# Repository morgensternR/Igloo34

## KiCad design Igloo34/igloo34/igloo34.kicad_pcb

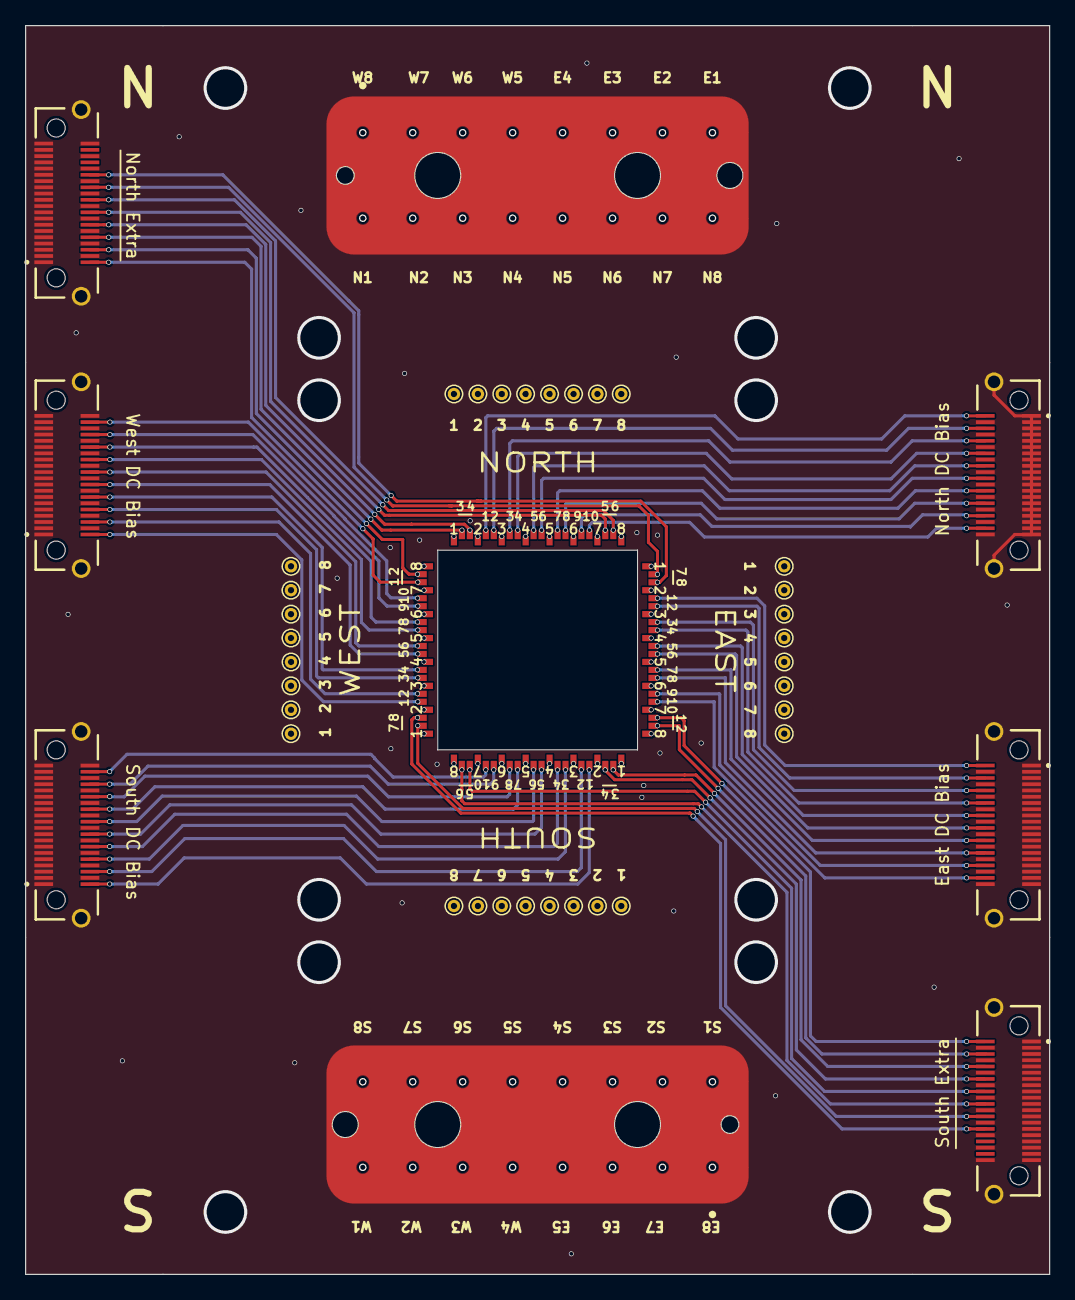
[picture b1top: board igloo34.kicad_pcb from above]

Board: 4 copper layers, 82.0 x 100.0 mm, 56 parts (0 on the bottom side), 89 nets.

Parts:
J1, J2, J5, J6: Conn_01x08_Pin; wirebond_8x_25mm
J3, J4: BE40A-S-92SP-2-2-08-0152; BE40A-S-92SP-X-2-08
J7, J8, J11, J12, J15, J20: LSHM-120-02.5-L-DV-A-S-TR; SAMTEC_LSHM-120-02.5-L-DV-A-S-TR
J9, J10, J13, J14: Conn_01x10; wirebond_10x_1cm
J16, J17, J18, J19, J21, J22, J23, J24: Conn_01x02; wirebond_2x_500um
TP1, TP2, TP3, TP4, TP5, TP6, TP7, TP8, TP9, TP10, TP11, TP12, TP13, TP14, TP15, TP16, TP17, TP18, TP19, TP20, TP21, TP22, TP23, TP24, TP25, TP26, TP27, TP28, TP29, TP30, TP31, TP32: TestPoint; Test point top pad

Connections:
GND: J3.S1 (SHIELD), J4.S1 (SHIELD), J7.01, J7.03, J7.04, J7.05, J7.07, J7.08, J7.09, J7.11, J7.12, J7.13, J7.15, J7.16, J7.17, J7.19, J7.20, J7.21, J7.23, J7.24, J7.25, J7.27, J7.28, J7.29, J7.31, J7.32, J7.33, J7.35, J7.36, J7.37, J7.39, J7.40, J7.S1 (SHIELD), J7.S2 (SHIELD), J8.01, J8.03, J8.04, J8.05, J8.07, J8.08, J8.09, J8.11, J8.12, J8.13, J8.15, J8.16, J8.17, J8.19, J8.20, J8.21, J8.23, J8.24, J8.25, J8.27, J8.28, J8.29, J8.31, J8.32, J8.33, J8.35, J8.36, J8.37, J8.39, J8.40, J8.S1 (SHIELD), J8.S2 (SHIELD), J11.01, J11.03, J11.04, J11.05, J11.07, J11.08, J11.09, J11.11, J11.12, J11.13, J11.15, J11.16, J11.17, J11.19, J11.20, J11.21, J11.23, J11.24, J11.25, J11.27, J11.28, J11.29, J11.31, J11.32, J11.33, J11.35, J11.36, J11.37, J11.39, J11.40, J11.S1 (SHIELD), J11.S2 (SHIELD), J12.01, J12.03, J12.04, J12.05, J12.07, J12.08, J12.09, J12.11, J12.12, J12.13, J12.15, J12.16, J12.17, J12.19, J12.20, J12.21, J12.23, J12.24, J12.25, J12.27, J12.28, J12.29, J12.31, J12.32, J12.33, J12.35, J12.36, J12.37, J12.39, J12.40, J12.S1 (SHIELD), J12.S2 (SHIELD), J15.01, J15.03, J15.04, J15.05, J15.07, J15.08, J15.09, J15.11, J15.12, J15.13, J15.15, J15.16, J15.17, J15.19, J15.20, J15.21, J15.23, J15.24, J15.25, J15.27, J15.28, J15.29, J15.31, J15.32, J15.33, J15.35, J15.36, J15.37, J15.39, J15.40, J15.S1 (SHIELD), J15.S2 (SHIELD), J20.01, J20.03, J20.04, J20.05, J20.07, J20.08, J20.09, J20.11, J20.12, J20.13, J20.15, J20.16, J20.17, J20.19, J20.20, J20.21, J20.23, J20.24, J20.25, J20.27, J20.28, J20.29, J20.31, J20.32, J20.33, J20.35, J20.36, J20.37, J20.39, J20.40, J20.S1 (SHIELD), J20.S2 (SHIELD)
unnamed: J1.1, J3.A01, TP32.1
unnamed: J1.2, J3.A02, TP31.1
unnamed: J1.3, J3.A03, TP30.1
unnamed: J1.4, J3.A04, TP29.1
unnamed: J1.5, J4.A05, TP20.1
unnamed: J1.6, J4.A06, TP19.1
unnamed: J1.7, J4.A07, TP18.1
unnamed: J1.8, J4.A08, TP17.1
unnamed: J2.1, J4.A01, TP24.1
unnamed: J2.2, J4.A02, TP23.1
unnamed: J2.3, J4.A03, TP22.1
unnamed: J2.4, J4.A04, TP21.1
unnamed: J2.5, J3.A05, TP28.1
unnamed: J2.6, J3.A06, TP27.1
unnamed: J2.7, J3.A07, TP26.1
unnamed: J2.8, J3.A08, TP25.1
unnamed: J3.B01, J5.1, TP9.1
unnamed: J3.B02, J5.2, TP10.1
unnamed: J3.B03, J5.3, TP11.1
unnamed: J3.B04, J5.4, TP12.1
unnamed: J3.B05, J5.5, TP13.1
unnamed: J3.B06, J5.6, TP14.1
unnamed: J3.B07, J5.7, TP15.1
unnamed: J3.B08, J5.8, TP16.1
unnamed: J4.B01, J6.1, TP2.1
unnamed: J4.B02, J6.2, TP1.1
unnamed: J4.B03, J6.3, TP3.1
unnamed: J4.B04, J6.4, TP4.1
unnamed: J4.B05, J6.5, TP5.1
unnamed: J4.B06, J6.6, TP6.1
unnamed: J4.B07, J6.7, TP7.1
unnamed: J4.B08, J6.8, TP8.1
unnamed: J7.02, J9.1
unnamed: J7.06, J9.2
unnamed: J7.10, J9.3
unnamed: J7.14, J9.4
unnamed: J7.18, J9.5
unnamed: J7.22, J9.6
unnamed: J7.26, J9.7
unnamed: J7.30, J9.8
unnamed: J7.34, J9.9
unnamed: J7.38, J9.10
unnamed: J8.02, J10.1
unnamed: J8.06, J10.2
unnamed: J8.10, J10.3
unnamed: J8.14, J10.4
unnamed: J8.18, J10.5
unnamed: J8.22, J10.6
unnamed: J8.26, J10.7
unnamed: J8.30, J10.8
unnamed: J8.34, J10.9
unnamed: J8.38, J10.10
unnamed: J11.02, J13.1
unnamed: J11.06, J13.2
unnamed: J11.10, J13.3
unnamed: J11.14, J13.4
unnamed: J11.18, J13.5
unnamed: J11.22, J13.6
unnamed: J11.26, J13.7
unnamed: J11.30, J13.8
unnamed: J11.34, J13.9
unnamed: J11.38, J13.10
unnamed: J12.02, J14.1
unnamed: J12.06, J14.2
unnamed: J12.10, J14.3
unnamed: J12.14, J14.4
unnamed: J12.18, J14.5
unnamed: J12.22, J14.6
unnamed: J12.26, J14.7
unnamed: J12.30, J14.8
unnamed: J12.34, J14.9
unnamed: J12.38, J14.10
unnamed: J15.02, J16.1
unnamed: J15.06, J16.2
unnamed: J15.10, J17.1
unnamed: J15.14, J17.2
unnamed: J15.18, J18.1
unnamed: J15.22, J18.2
unnamed: J15.26, J19.1
unnamed: J15.30, J19.2
unnamed: J20.02, J21.1
unnamed: J20.06, J21.2
unnamed: J20.10, J22.1
unnamed: J20.14, J22.2
unnamed: J20.18, J23.1
unnamed: J20.22, J23.2
unnamed: J20.26, J24.1
unnamed: J20.30, J24.2

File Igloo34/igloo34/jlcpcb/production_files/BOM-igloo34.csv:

Comment,Designator,Footprint,LCSC
LSHM-120-02.5-L-DV-A-S-TR,"J11,J12,J15,J20,J7,J8",SAMTEC_LSHM-120-02.5-L-DV-A-S-TR,C3654193
BE40A-S-92SP-2-2-08-0152,J3,BE40A-S-92SP-X-2-08,
TestPoint,TP32,Test point top pad,
TestPoint,TP31,Test point top pad,
TestPoint,TP30,Test point top pad,
TestPoint,TP29,Test point top pad,
TestPoint,TP28,Test point top pad,
TestPoint,TP27,Test point top pad,
TestPoint,TP26,Test point top pad,
TestPoint,TP25,Test point top pad,
TestPoint,TP24,Test point top pad,
TestPoint,TP23,Test point top pad,
TestPoint,TP22,Test point top pad,
TestPoint,TP21,Test point top pad,
TestPoint,TP20,Test point top pad,
TestPoint,TP19,Test point top pad,
TestPoint,TP18,Test point top pad,
TestPoint,TP17,Test point top pad,
TestPoint,TP16,Test point top pad,
TestPoint,TP15,Test point top pad,
TestPoint,TP14,Test point top pad,
TestPoint,TP13,Test point top pad,
TestPoint,TP12,Test point top pad,
TestPoint,TP11,Test point top pad,
TestPoint,TP10,Test point top pad,
TestPoint,TP9,Test point top pad,
TestPoint,TP8,Test point top pad,
TestPoint,TP7,Test point top pad,
TestPoint,TP6,Test point top pad,
TestPoint,TP5,Test point top pad,
TestPoint,TP4,Test point top pad,
TestPoint,TP3,Test point top pad,
TestPoint,TP2,Test point top pad,
TestPoint,TP1,Test point top pad,
Conn_01x02,J21,wirebond_2x_500um,
Conn_01x02,J17,wirebond_2x_500um,
Conn_01x08_Pin,J6,wirebond_8x_25mm,
Conn_01x02,J24,wirebond_2x_500um,
Conn_01x02,J18,wirebond_2x_500um,
Conn_01x02,J19,wirebond_2x_500um,
Conn_01x08_Pin,J2,wirebond_8x_25mm,
Conn_01x02,J23,wirebond_2x_500um,
Conn_01x02,J22,wirebond_2x_500um,
Conn_01x08_Pin,J5,wirebond_8x_25mm,
Conn_01x02,J16,wirebond_2x_500um,
Conn_01x10,J10,wirebond_10x_1cm,
Conn_01x10,J14,wirebond_10x_1cm,
Conn_01x10,J9,wirebond_10x_1cm,
BE40A-S-92SP-2-2-08-0152,J4,BE40A-S-92SP-X-2-08,
Conn_01x08_Pin,J1,wirebond_8x_25mm,
Conn_01x10,J13,wirebond_10x_1cm,

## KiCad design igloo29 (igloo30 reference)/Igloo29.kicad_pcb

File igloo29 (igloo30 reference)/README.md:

# Project/path setup
- Open amcc-template.kicad_pro, save as new project name

# Adding footprint+symbols
- Any footprint files added to /project-footprints/ will be added automatically to the "project-footprints" library
- Add any kicad_sym files to /project-symbols/ and add their path directly to Symbol Libraries:  Menu->Preferences->Manage Symbol Libraries
    - Suggested name:  "project-symbols2", "project-symbols3", etc
    - Whenever searching for symbols/footprints, just type "project" in the search bar

# To insert your new symbol + footprint
- Click Add Symbol button on right
- Navigate to e.g. "project-symbols2" and select the symbol
- Place the device, and double-click it to open properties
- Edit the "Footprint" field and navigate to e.g. "project-footprints" to select the footprint

# Before starting
- PCBNew->Menu->File->Board Setup
    - Physical Stackup -> 2 or 4 layers
    - Net Classes:
        - JLCPCB Stripline 50 Ohm trace width = 0.35mm wide
        - Via size/hole = 0.6mm/0.4mm

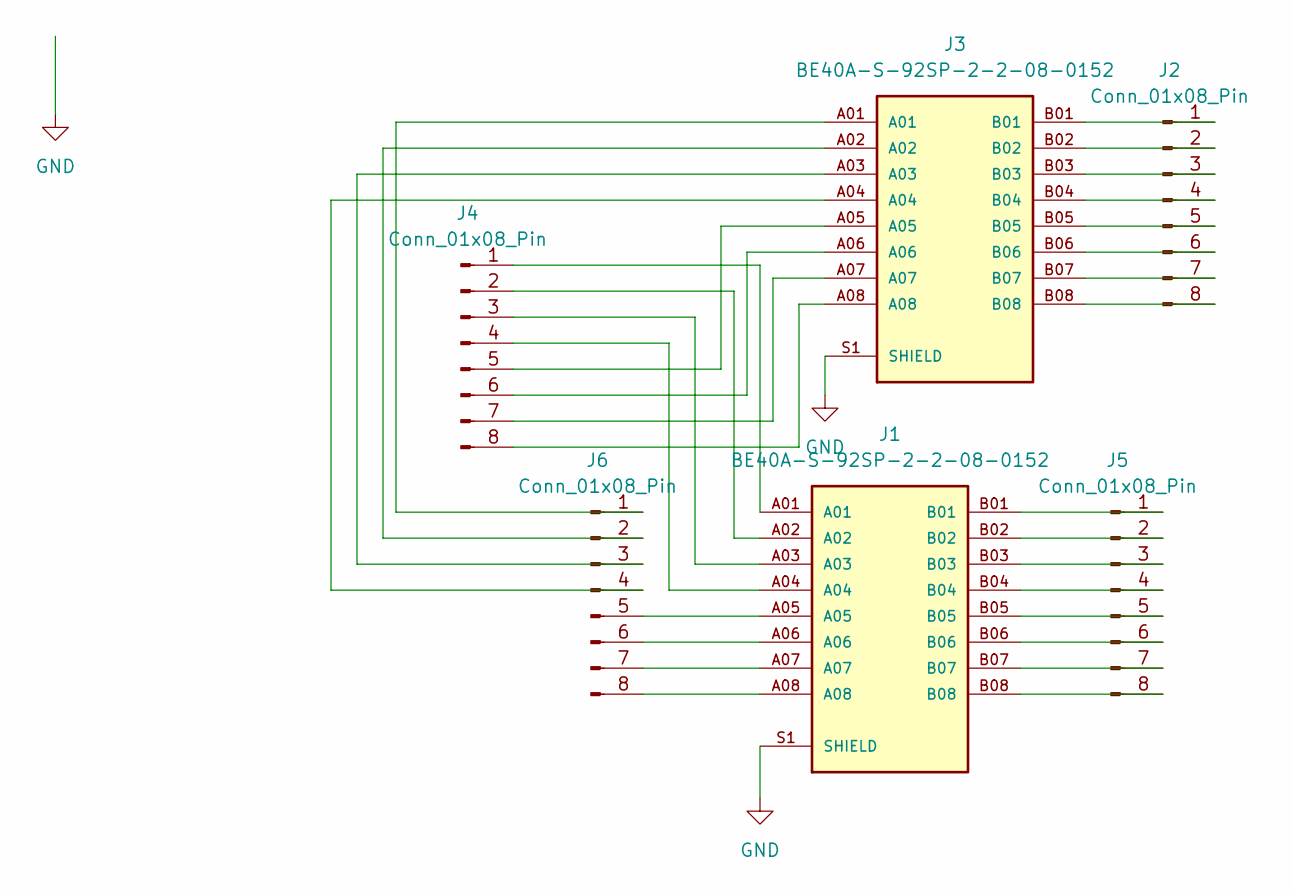
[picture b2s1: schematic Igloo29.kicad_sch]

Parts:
J1, J3: BE40A-S-92SP-2-2-08-0152; BE40A-S-92SP-X-2-08
J2, J4, J5, J6: Conn_01x08_Pin; wirebond_8x_25mm

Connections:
GND: J1.S1 (SHIELD), J3.S1 (SHIELD)
unnamed: J2.1, J3.B01
unnamed: J2.2, J3.B02
unnamed: J2.3, J3.B03
unnamed: J2.4, J3.B04
unnamed: J2.5, J3.B05
unnamed: J2.6, J3.B06
unnamed: J2.7, J3.B07
unnamed: J2.8, J3.B08
unnamed: J1.A01, J4.1
unnamed: J1.A02, J4.2
unnamed: J1.A03, J4.3
unnamed: J1.A04, J4.4
unnamed: J3.A05, J4.5
unnamed: J3.A06, J4.6
unnamed: J3.A07, J4.7
unnamed: J3.A08, J4.8
unnamed: J1.B01, J5.1
unnamed: J1.B02, J5.2
unnamed: J1.B03, J5.3
unnamed: J1.B04, J5.4
unnamed: J1.B05, J5.5
unnamed: J1.B06, J5.6
unnamed: J1.B07, J5.7
unnamed: J1.B08, J5.8
unnamed: J3.A01, J6.1
unnamed: J3.A02, J6.2
unnamed: J3.A03, J6.3
unnamed: J3.A04, J6.4
unnamed: J1.A05, J6.5
unnamed: J1.A06, J6.6
unnamed: J1.A07, J6.7
unnamed: J1.A08, J6.8

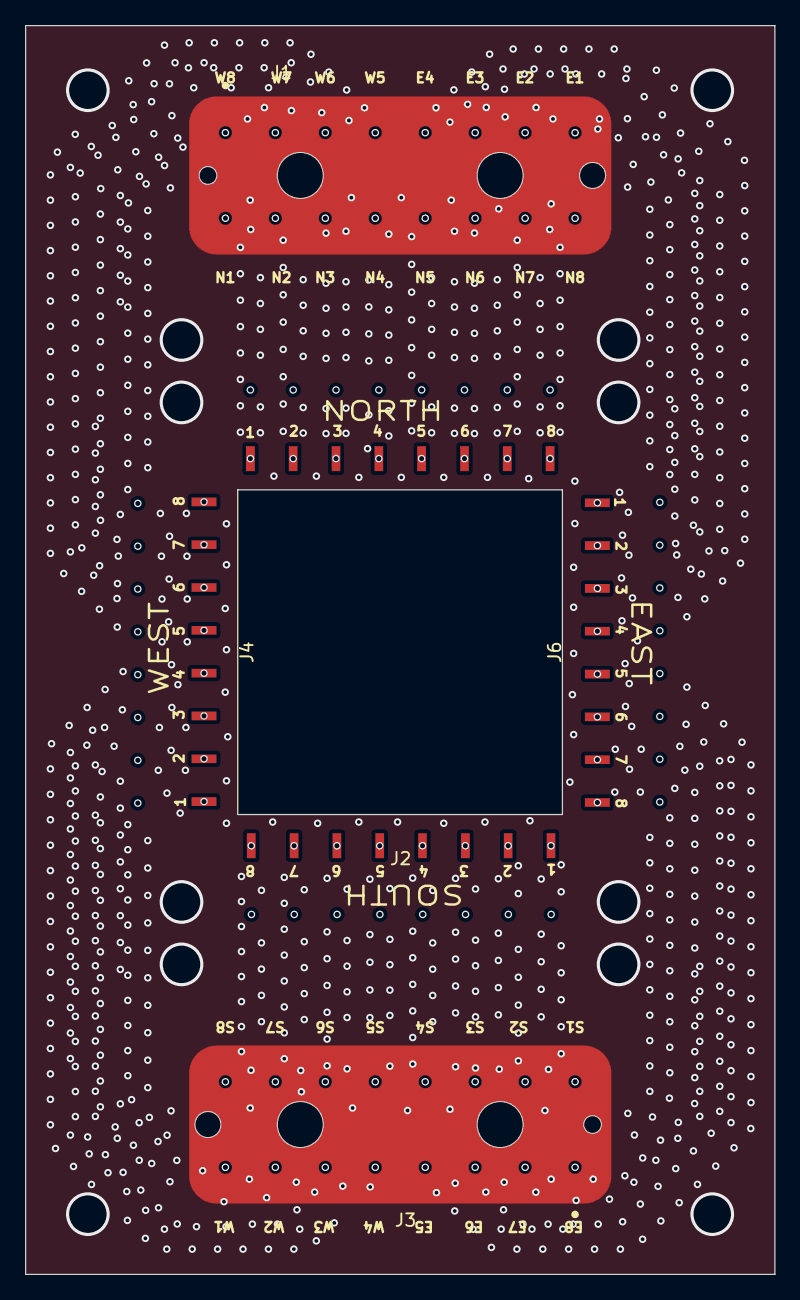
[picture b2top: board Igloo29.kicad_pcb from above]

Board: 4 copper layers, 60.0 x 100.0 mm, 6 parts (0 on the bottom side), 33 nets.

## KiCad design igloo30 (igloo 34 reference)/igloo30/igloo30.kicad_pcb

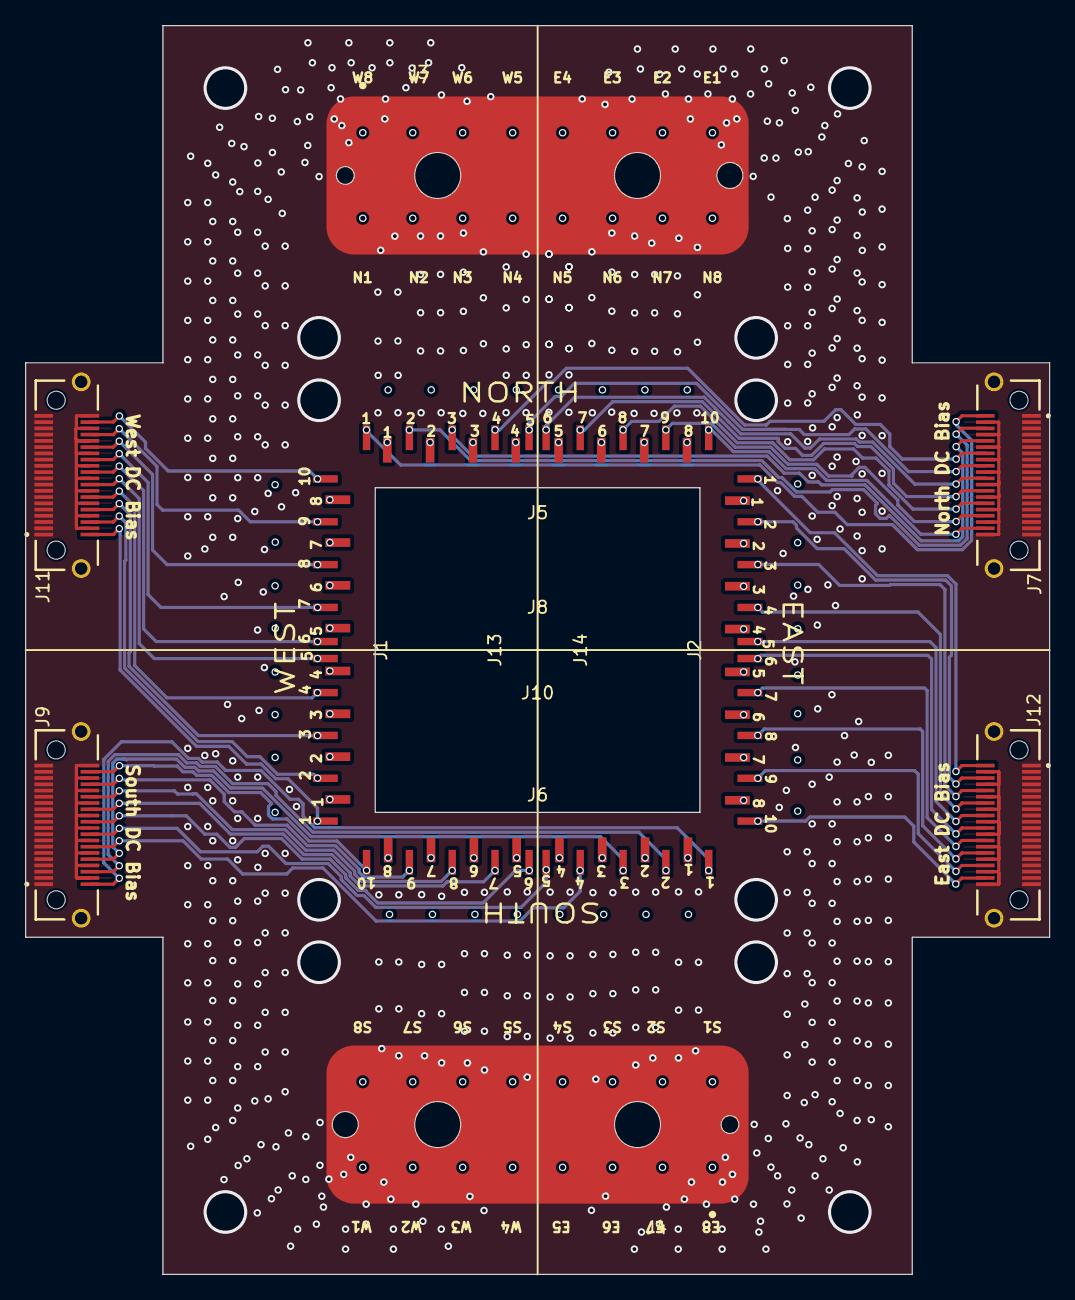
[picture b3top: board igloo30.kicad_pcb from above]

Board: 4 copper layers, 82.0 x 100.0 mm, 14 parts (0 on the bottom side), 73 nets.

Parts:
J1, J2, J5, J6: Conn_01x08_Pin; wirebond_8x_25mm
J3, J4: BE40A-S-92SP-2-2-08-0152; BE40A-S-92SP-X-2-08
J7, J9, J11, J12: LSHM-120-02.5-L-DV-A-S-TR; SAMTEC_LSHM-120-02.5-L-DV-A-S-TR
J8, J10, J13, J14: Conn_01x10; wirebond_10x_1cm

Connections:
GND: J3.S1 (SHIELD), J4.S1 (SHIELD), J7.01, J7.03, J7.04, J7.05, J7.07, J7.08, J7.09, J7.11, J7.12, J7.13, J7.15, J7.16, J7.17, J7.19, J7.20, J7.21, J7.23, J7.24, J7.25, J7.27, J7.28, J7.29, J7.31, J7.32, J7.33, J7.35, J7.36, J7.37, J7.39, J7.40, J7.S1 (SHIELD), J7.S2 (SHIELD), J9.01, J9.03, J9.04, J9.05, J9.07, J9.08, J9.09, J9.11, J9.12, J9.13, J9.15, J9.16, J9.17, J9.19, J9.20, J9.21, J9.23, J9.24, J9.25, J9.27, J9.28, J9.29, J9.31, J9.32, J9.33, J9.35, J9.36, J9.37, J9.39, J9.40, J9.S1 (SHIELD), J9.S2 (SHIELD), J11.01, J11.03, J11.04, J11.05, J11.07, J11.08, J11.09, J11.11, J11.12, J11.13, J11.15, J11.16, J11.17, J11.19, J11.20, J11.21, J11.23, J11.24, J11.25, J11.27, J11.28, J11.29, J11.31, J11.32, J11.33, J11.35, J11.36, J11.37, J11.39, J11.40, J11.S1 (SHIELD), J11.S2 (SHIELD), J12.01, J12.03, J12.04, J12.05, J12.07, J12.08, J12.09, J12.11, J12.12, J12.13, J12.15, J12.16, J12.17, J12.19, J12.20, J12.21, J12.23, J12.24, J12.25, J12.27, J12.28, J12.29, J12.31, J12.32, J12.33, J12.35, J12.36, J12.37, J12.39, J12.40, J12.S1 (SHIELD), J12.S2 (SHIELD)
unnamed: J1.1, J3.A01
unnamed: J1.2, J3.A02
unnamed: J1.3, J3.A03
unnamed: J1.4, J3.A04
unnamed: J1.5, J4.A05
unnamed: J1.6, J4.A06
unnamed: J1.7, J4.A07
unnamed: J1.8, J4.A08
unnamed: J2.1, J4.A01
unnamed: J2.2, J4.A02
unnamed: J2.3, J4.A03
unnamed: J2.4, J4.A04
unnamed: J2.5, J3.A05
unnamed: J2.6, J3.A06
unnamed: J2.7, J3.A07
unnamed: J2.8, J3.A08
unnamed: J3.B01, J5.1
unnamed: J3.B02, J5.2
unnamed: J3.B03, J5.3
unnamed: J3.B04, J5.4
unnamed: J3.B05, J5.5
unnamed: J3.B06, J5.6
unnamed: J3.B07, J5.7
unnamed: J3.B08, J5.8
unnamed: J4.B01, J6.1
unnamed: J4.B02, J6.2
unnamed: J4.B03, J6.3
unnamed: J4.B04, J6.4
unnamed: J4.B05, J6.5
unnamed: J4.B06, J6.6
unnamed: J4.B07, J6.7
unnamed: J4.B08, J6.8
unnamed: J7.02, J8.1
unnamed: J7.06, J8.2
unnamed: J7.10, J8.3
unnamed: J7.14, J8.4
unnamed: J7.18, J8.5
unnamed: J7.22, J8.6
unnamed: J7.26, J8.7
unnamed: J7.30, J8.8
unnamed: J7.34, J8.9
unnamed: J7.38, J8.10
unnamed: J9.02, J10.1
unnamed: J9.06, J10.2
unnamed: J9.10, J10.3
unnamed: J9.14, J10.4
unnamed: J9.18, J10.5
unnamed: J9.22, J10.6
unnamed: J9.26, J10.7
unnamed: J9.30, J10.8
unnamed: J9.34, J10.9
unnamed: J9.38, J10.10
unnamed: J11.02, J13.1
unnamed: J11.06, J13.2
unnamed: J11.10, J13.3
unnamed: J11.14, J13.4
unnamed: J11.18, J13.5
unnamed: J11.22, J13.6
unnamed: J11.26, J13.7
unnamed: J11.30, J13.8
unnamed: J11.34, J13.9
unnamed: J11.38, J13.10
unnamed: J12.02, J14.1
unnamed: J12.06, J14.2
unnamed: J12.10, J14.3
unnamed: J12.14, J14.4
unnamed: J12.18, J14.5
unnamed: J12.22, J14.6
unnamed: J12.26, J14.7
unnamed: J12.30, J14.8
unnamed: J12.34, J14.9
unnamed: J12.38, J14.10

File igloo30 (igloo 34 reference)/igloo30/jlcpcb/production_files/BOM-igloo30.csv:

Comment,Designator,Footprint,LCSC
LSHM-120-02.5-L-DV-A-S-TR,J12,SAMTEC_LSHM-120-02.5-L-DV-A-S-TR,
Conn_01x10,J10,wirebond_10x_1cm,
Conn_01x10,J14,wirebond_10x_1cm,
Conn_01x08_Pin,J1,wirebond_8x_25mm,
LSHM-120-02.5-L-DV-A-S-TR,J11,SAMTEC_LSHM-120-02.5-L-DV-A-S-TR,
LSHM-120-02.5-L-DV-A-S-TR,J7,SAMTEC_LSHM-120-02.5-L-DV-A-S-TR,
Conn_01x08_Pin,J6,wirebond_8x_25mm,
Conn_01x10,J8,wirebond_10x_1cm,
Conn_01x08_Pin,J5,wirebond_8x_25mm,
Conn_01x08_Pin,J2,wirebond_8x_25mm,
BE40A-S-92SP-2-2-08-0152,J3,BE40A-S-92SP-X-2-08,
LSHM-120-02.5-L-DV-A-S-TR,J9,SAMTEC_LSHM-120-02.5-L-DV-A-S-TR,
BE40A-S-92SP-2-2-08-0152,J4,BE40A-S-92SP-X-2-08,
Conn_01x10,J13,wirebond_10x_1cm,

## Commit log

2024-08-26 increased via sizes
